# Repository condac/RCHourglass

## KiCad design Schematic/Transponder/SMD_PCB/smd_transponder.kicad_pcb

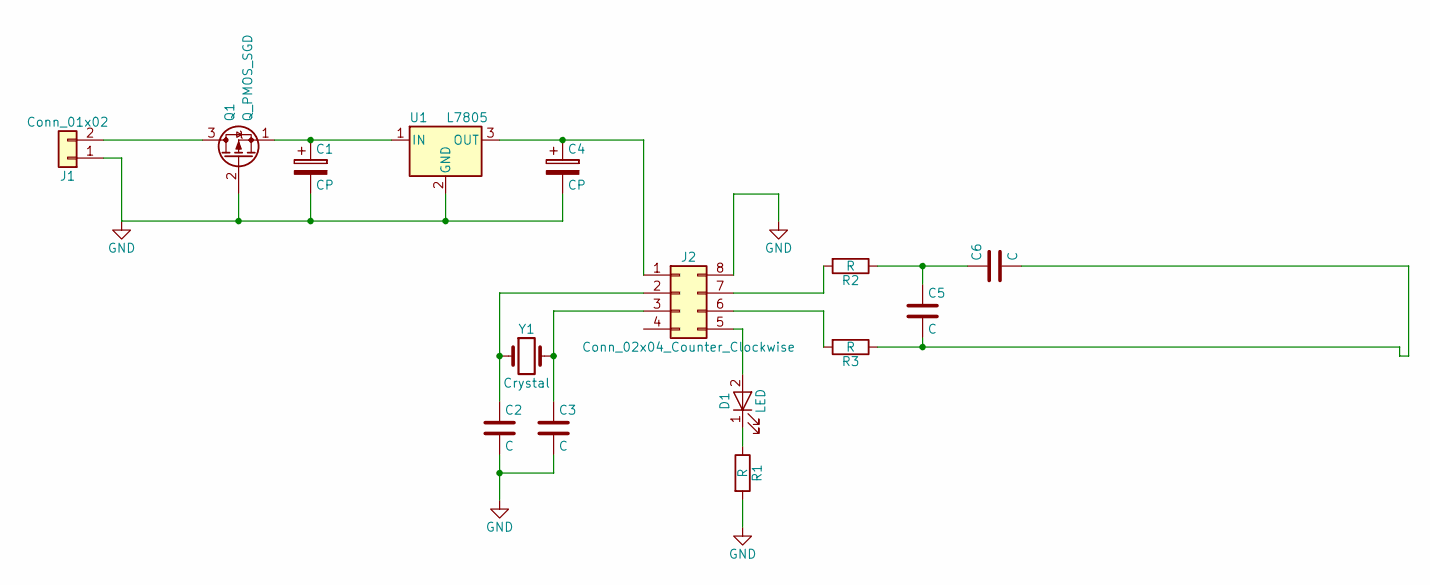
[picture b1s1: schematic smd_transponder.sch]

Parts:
C1, C4: CP; CP_Tantalum_Case-A_EIA-3216-18_Reflow
C2, C3, C5, C6: C; C_0805
D1: LED; LED_0805
J1: Conn_01x02; Pin_Header_Straight_1x02_Pitch2.54mm
J2: Conn_02x04_Counter_Clockwise; SOIC-8_3.9x4.9mm_Pitch1.27mm
Q1: Q_PMOS_SGD; SOT-23
R1, R2, R3: R; R_0805
U1: L7805; SOT-89-3
Y1: Crystal; Crystal_HC49-4H_Vertical

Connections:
GND: C1.2, C2.2, C3.2, C4.2, J1.1, J2.8, Q1.2 (G), R1.2, U1.2 (GND)
unnamed: C1.1, Q1.1 (S), U1.1 (IN)
unnamed: C2.1, J2.2, Y1.1
unnamed: C3.1, J2.3, Y1.2
unnamed: C4.1, J2.1, U1.3 (OUT)
unnamed: C5.1, C6.1, R2.1
unnamed: C5.2, C6.2, R3.1
unnamed: D1.1 (K), R1.1
unnamed: D1.2 (A), J2.5
unnamed: J1.2, Q1.3 (D)
unnamed: J2.6, R3.2
unnamed: J2.7, R2.2

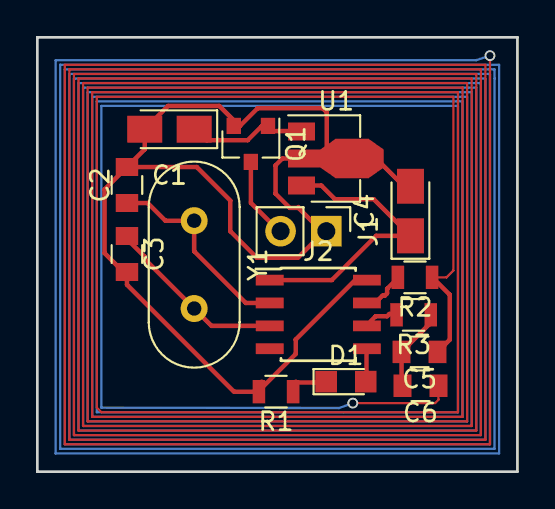
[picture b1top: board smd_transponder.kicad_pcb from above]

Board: 2 copper layers, 26.7 x 24.1 mm, 15 parts (0 on the bottom side), 12 nets.

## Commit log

2018-05-25 PCB with SMD components and antenna
